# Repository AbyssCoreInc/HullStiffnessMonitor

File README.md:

# HullStiffnessMonitor
Simple Raspberry Pi Zero based device for monitoring and recording sailboat hull stiffness

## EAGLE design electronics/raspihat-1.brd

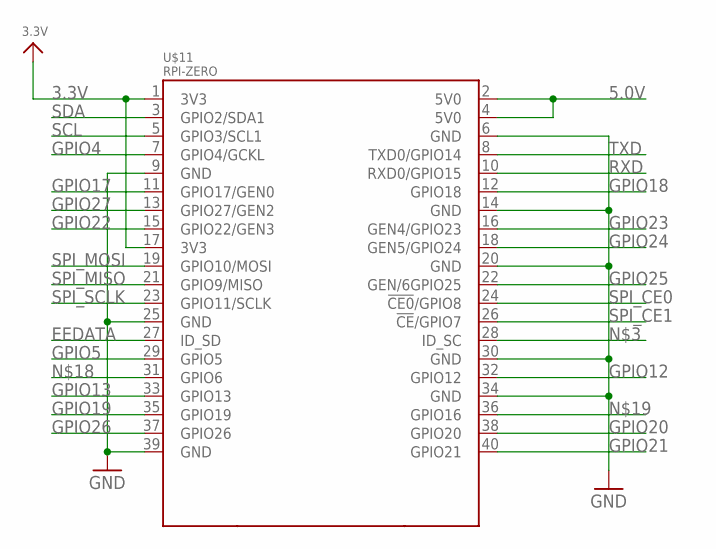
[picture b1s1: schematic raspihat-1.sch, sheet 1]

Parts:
U$11: RPI-ZERO; RASPBERRYPI_BASTELSTUBE_V13_RASPI_BOARD_B+_FULL

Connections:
3.3V: U$11.1 (3V3), U$11.17 (3V3); also elsewhere on the board
5.0V: U$11.2 (5V0), U$11.4 (5V0); also elsewhere on the board
EEDATA: U$11.27 (ID_SD)
GND: U$11.6 (GND), U$11.9 (GND), U$11.14 (GND), U$11.20 (GND), U$11.25 (GND), U$11.30 (GND), U$11.34 (GND), U$11.39 (GND); also elsewhere on the board
GPIO4: U$11.7 (GPIO4/GCKL); also elsewhere on the board
GPIO5: U$11.29 (GPIO5)
GPIO12: U$11.32 (GPIO12)
GPIO13: U$11.33 (GPIO13)
GPIO17: U$11.11 (GPIO17/GEN0); also elsewhere on the board
GPIO18: U$11.12 (GPIO18); also elsewhere on the board
GPIO19: U$11.35 (GPIO19)
GPIO20: U$11.38 (GPIO20)
GPIO21: U$11.40 (GPIO21); also elsewhere on the board
GPIO22: U$11.15 (GPIO22/GEN3)
GPIO23: U$11.16 (GEN4/GPIO23)
GPIO24: U$11.18 (GEN5/GPIO24)
GPIO25: U$11.22 (GEN/6GPIO25); also elsewhere on the board
GPIO26: U$11.37 (GPIO26); also elsewhere on the board
GPIO27: U$11.13 (GPIO27/GEN2)
RXD: U$11.10 (RXD0/GPIO15)
SCL: U$11.5 (GPIO3/SCL1); also elsewhere on the board
SDA: U$11.3 (GPIO2/SDA1); also elsewhere on the board
SPI_CE0: U$11.24 (!CE0!/GPIO8)
SPI_CE1: U$11.26 (!CE!/GPIO7)
SPI_MISO: U$11.21 (GPIO9/MISO)
SPI_MOSI: U$11.19 (GPIO10/MOSI)
SPI_SCLK: U$11.23 (GPIO11/SCLK)
TXD: U$11.8 (TXD0/GPIO14)

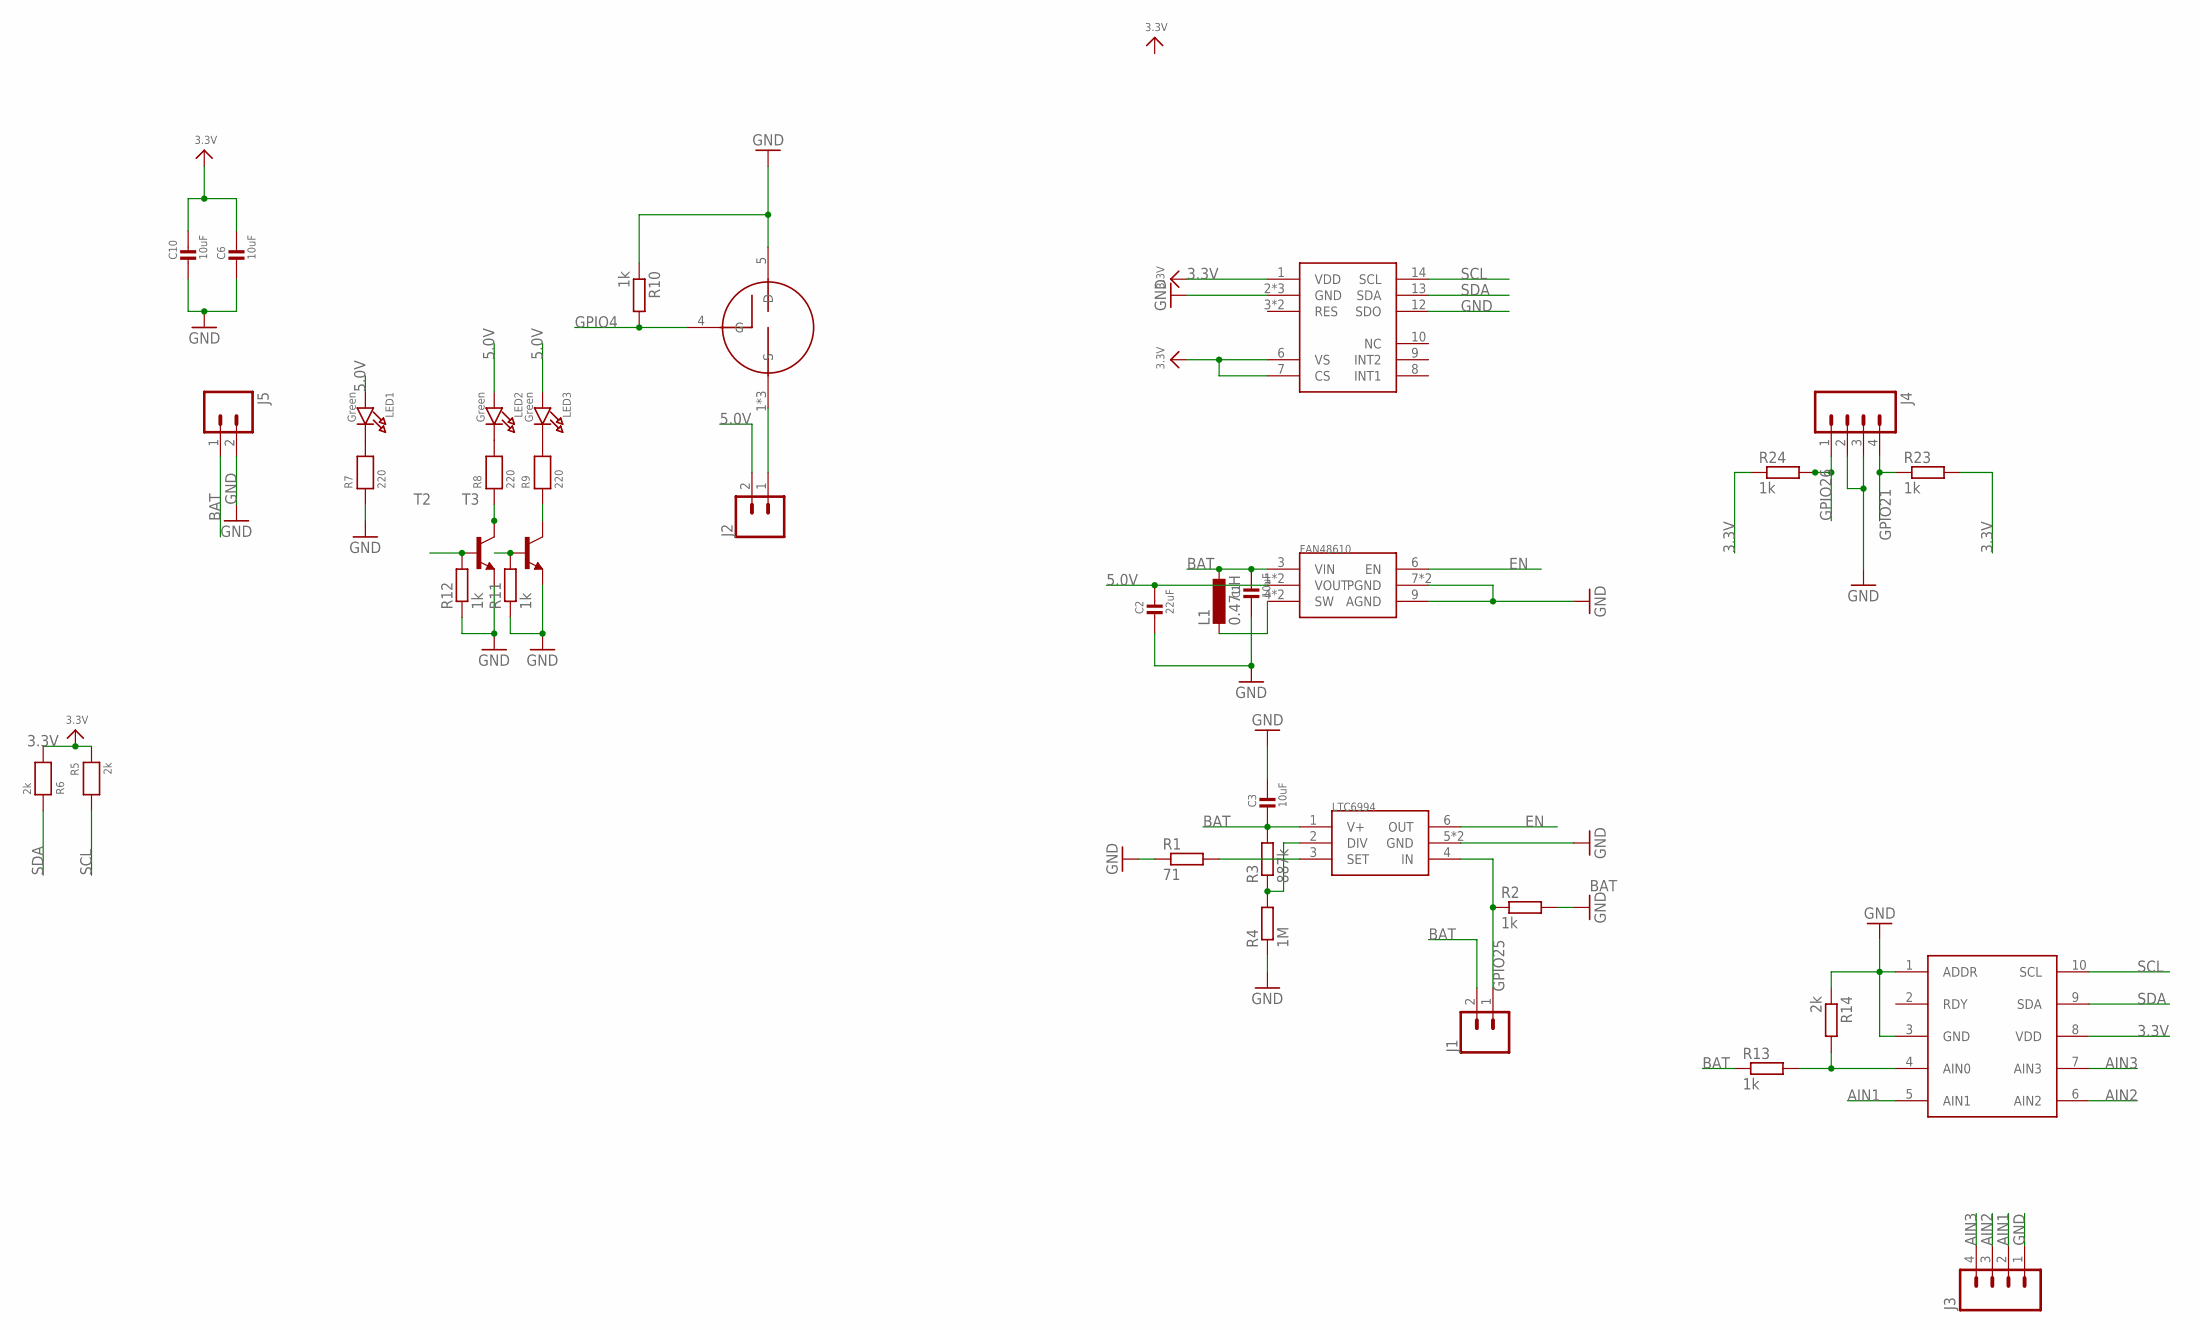
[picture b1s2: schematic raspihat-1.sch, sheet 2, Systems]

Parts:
C1, C3, C6, C10: 10uF; 0805-NO
C2: 22uF; 0805-NO
J1, J2: CONN_02; 1X02
J3, J4: M04JST; 1X04-1.5MM_JST
J5: M02PTH; 1X02
L1: 0.47uH; L2012C
LED1, LED2, LED3: Green; CHIPLED_0805_NOOUTLINE
R1: 71; R0603
R2, R10, R11, R12, R13, R23, R24: 1k; R0805
R3: 887k; R0603
R4: 1M; R0805
R5, R6: 2k; 0805-NO
R7, R8, R9: 220; 0805-NO
R14: 2k; R0805
T2, T3: MMBT6517LT1-NPN-SOT23-BEC; SOT23-BEC
U$3: ADXL345; LGA14
U$5: FAN48610; WLCSP-9
U$6: LTC6994; DFN-6
U$8: BUK9M; LFPAK33
U$15: ADS1015; VSSOP10

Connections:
3.3V: C6.1, C10.1, R5.1, R6.2, R23.2, R24.1, U$3.1 (VDD), U$3.6 (VS), U$3.7 (CS), U$15.8 (VDD); also elsewhere on the board
5.0V: C2.1, J2.2, LED1.A, LED2.A, LED3.A, U$5.1 (VOUT), U$5.2 (VOUT); also elsewhere on the board
AIN1: J3.2, U$15.5 (AIN1)
AIN2: J3.3, U$15.6 (AIN2)
AIN3: J3.4, U$15.7 (AIN3)
BAT: C1.1, C3.2, J1.2, J5.1, L1.1, R3.2, R13.1, U$5.3 (VIN), U$6.1 (V+)
EN: U$5.6 (EN), U$6.6 (OUT)
GND: C1.2, C2.2, C3.1, C6.2, C10.2, J3.1, J4.2, J4.3, J5.2, R1.1, R2.2, R4.1, R7.1, R10.1, R11.1, R12.1, R14.1, T2.E, T3.E, U$3.2 (GND), U$3.4 (GND), U$3.5 (GND), U$3.12 (SDO), U$5.7 (PGND), U$5.8 (PGND), U$5.9 (AGND), U$6.5 (GND), U$6.P$1 (GND), U$8.5 (D), U$15.1 (ADDR), U$15.3 (GND); also elsewhere on the board
GPIO4: R10.2, U$8.4 (G); also elsewhere on the board
GPIO17: R12.2, T2.B; also elsewhere on the board
GPIO18: R11.2, T3.B; also elsewhere on the board
GPIO21: J4.4, R23.1; also elsewhere on the board
GPIO25: J1.1, R2.1, U$6.4 (IN); also elsewhere on the board
GPIO26: J4.1, R24.2; also elsewhere on the board
unnamed: R1.2, U$6.3 (SET)
unnamed: R3.1, R4.2, U$6.2 (DIV)
unnamed: R13.2, R14.2, U$15.4 (AIN0)
unnamed: L1.2, U$5.4 (SW), U$5.5 (SW)
unnamed: LED2.C, R8.2
unnamed: LED3.C, R9.2
unnamed: R8.1, T2.C
unnamed: R9.1, T3.C
unnamed: J2.1, U$8.1 (S), U$8.2 (S), U$8.3 (S)
unnamed: LED1.C, R7.2
SCL: R5.2, U$3.14 (SCL), U$15.10 (SCL); also elsewhere on the board
SDA: R6.1, U$3.13 (SDA), U$15.9 (SDA); also elsewhere on the board

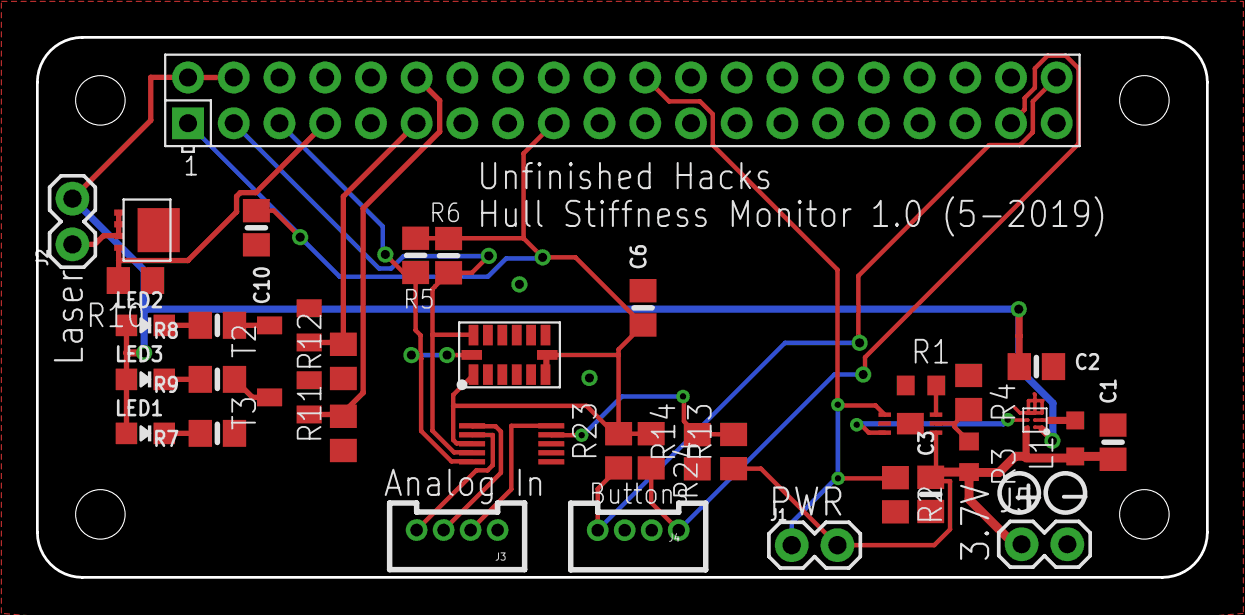
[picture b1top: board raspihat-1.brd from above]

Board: 2 copper layers, 65.0 x 30.0 mm, 38 parts (0 on the bottom side), 26 nets.

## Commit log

2019-05-27 initial checkin, not much working yet
2019-05-27 basic frame for probe python implementation
2019-05-27 initial python implementation example
2019-06-14 added object detection stub
2019-06-14 added GPIO setup and power off command
2019-06-17 Changes to laser detection
2019-06-17 some updates to messaging including service discovery via Zeroconf
2019-06-18 oneway trafic now works somehow
2019-06-19 Improved communication features, calibration still missing
2019-06-20 calibration working now somehow, buttons still not used...
2019-06-25 android software update
2019-06-26 added System service file for probe
2019-06-27 fixed an issue of depending probe on video0 device on bootup

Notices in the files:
parts and their libraries:
microbuilder: This work is placed in the public domain, and may be freely used for commercial and non-commercial work with the following conditions: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
SparkFun-Connectors: Licensing: Creative Commons ShareAlike 4.0 International - https://creativecommons.org/licenses/by-sa/4.0
